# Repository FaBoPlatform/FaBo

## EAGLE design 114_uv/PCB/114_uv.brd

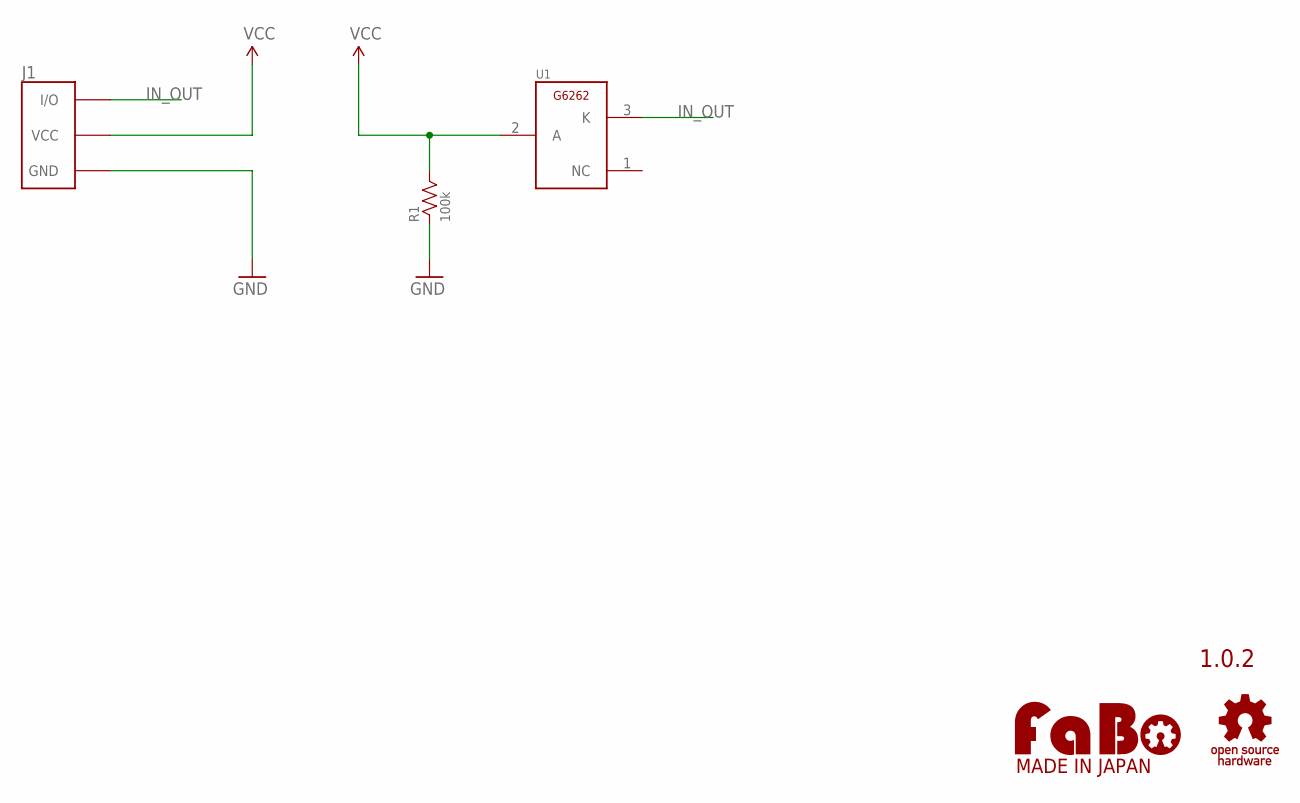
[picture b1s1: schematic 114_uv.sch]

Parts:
J1: FABO_BRICK_3PIN
R1: 100k; 0603
U1: HAMAMATSU-GAASP-G6262; GAASP-G6262
U$2: LOGO_OSHW-M_BOTTOM; LOGO_OSHW_M_BOTTOM
U$3: LOGO_FABO-M; LOGO_FABO_MS

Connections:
GND: J1.GND, R1.1
IN_OUT: J1.I/O, U1.3 (K)
VCC: J1.VCC, R1.2, U1.2 (A)

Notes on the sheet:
1.0.2

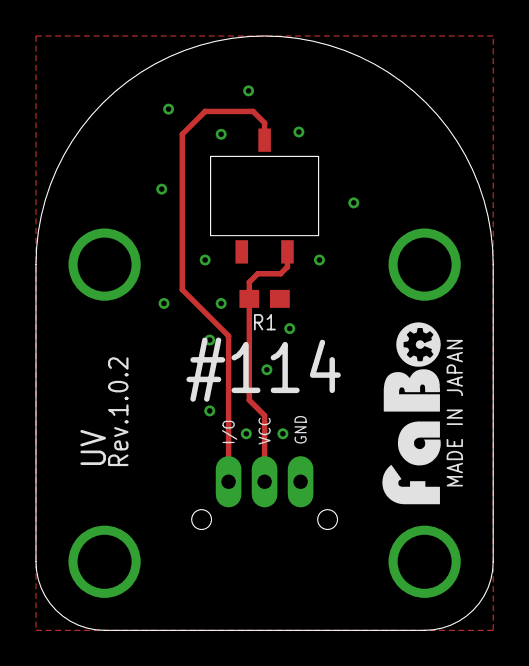
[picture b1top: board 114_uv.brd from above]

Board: 2 copper layers, 25.4 x 33.0 mm, 5 parts (0 on the bottom side), 3 nets.

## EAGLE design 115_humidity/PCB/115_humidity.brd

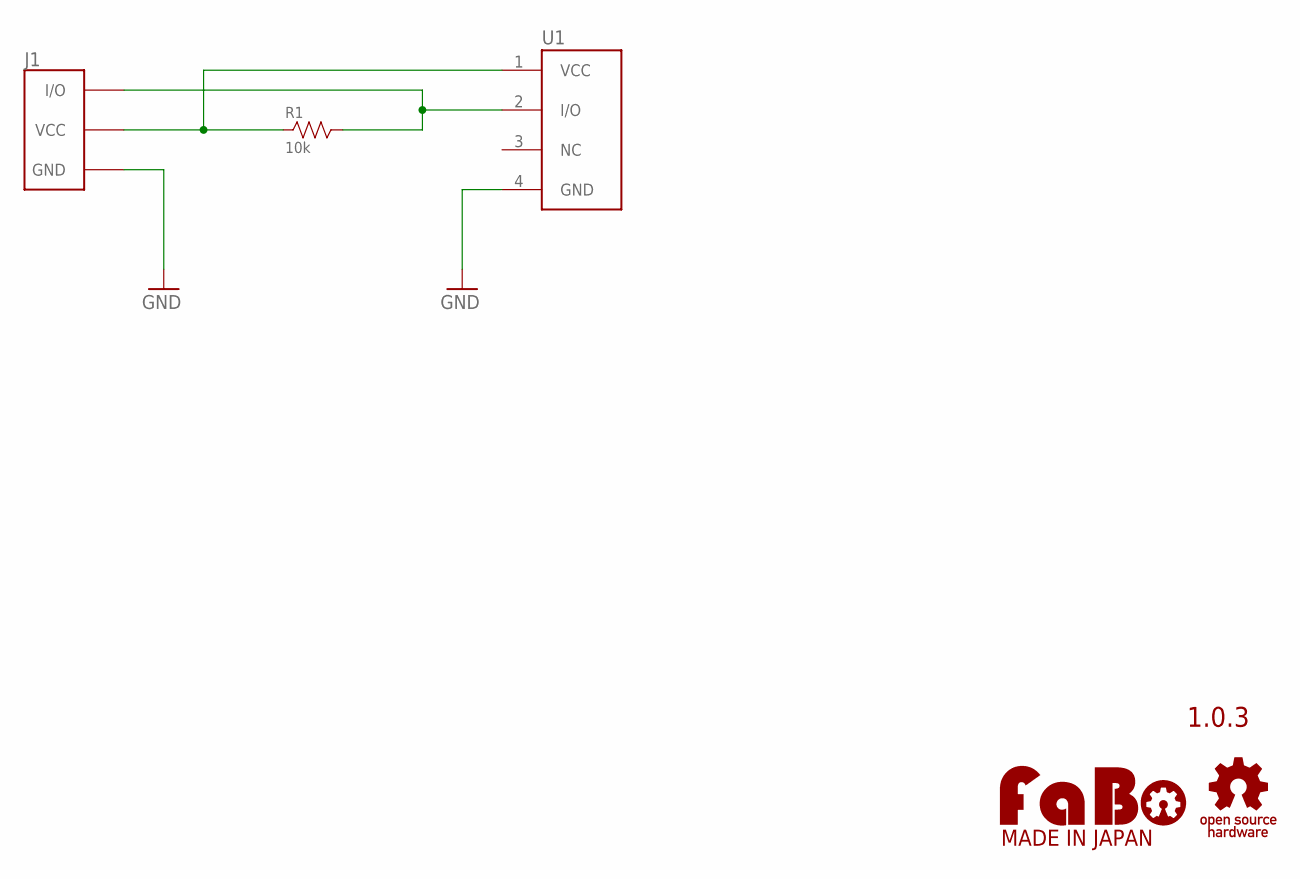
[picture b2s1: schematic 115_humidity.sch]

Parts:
J1: FABO_BRICK_3PIN
R1: 10k; AXL-REGULAR
U1: DHT11
U$2: LOGO_OSHW-M_BOTTOM; LOGO_OSHW_M_BOTTOM
U$3: LOGO_FABO-M; LOGO_FABO_MS

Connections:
GND: J1.GND, U1.4 (GND)
unnamed: J1.I/O, R1.2, U1.2 (I/O)
unnamed: J1.VCC, R1.1, U1.1 (VCC)

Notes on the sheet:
1.0.3

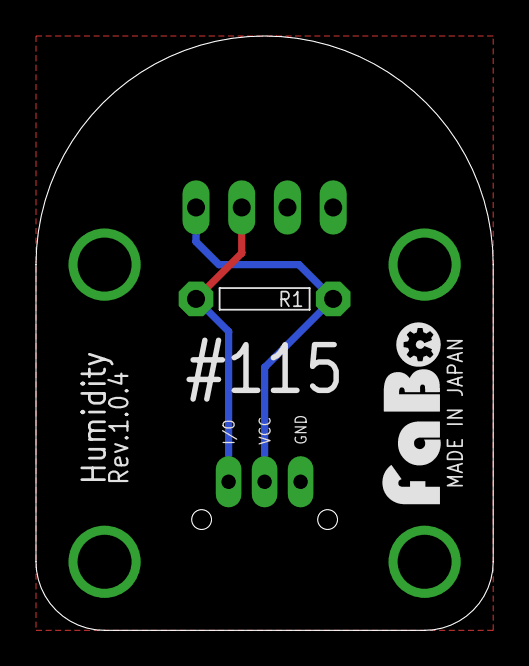
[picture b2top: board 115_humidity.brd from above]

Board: 2 copper layers, 25.4 x 33.0 mm, 5 parts (0 on the bottom side), 3 nets.

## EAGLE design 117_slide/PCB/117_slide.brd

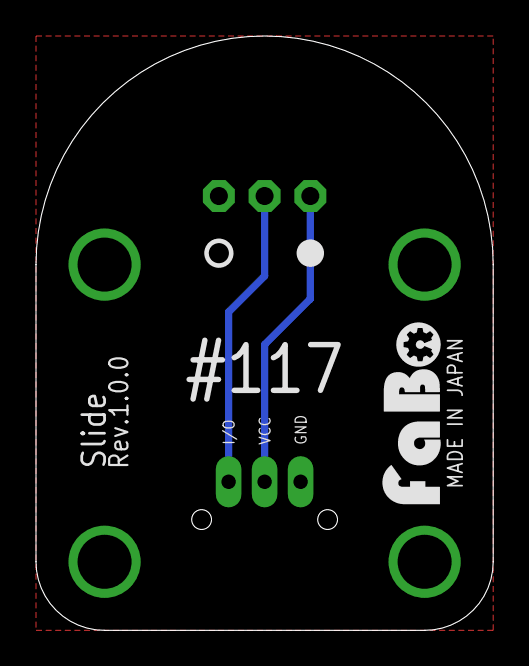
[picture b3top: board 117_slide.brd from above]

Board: 2 copper layers, 25.4 x 33.0 mm, 4 parts (0 on the bottom side), 3 nets.

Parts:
J1: FABO_BRICK_3PIN
SW1: EG1218
U$2: LOGO_OSHW_M_BOTTOM
U$4: LOGO_FABO_MS

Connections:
GND: J1.GND, SW1.1
IO: J1.I/O, SW1.2
VCC: J1.VCC, SW1.3

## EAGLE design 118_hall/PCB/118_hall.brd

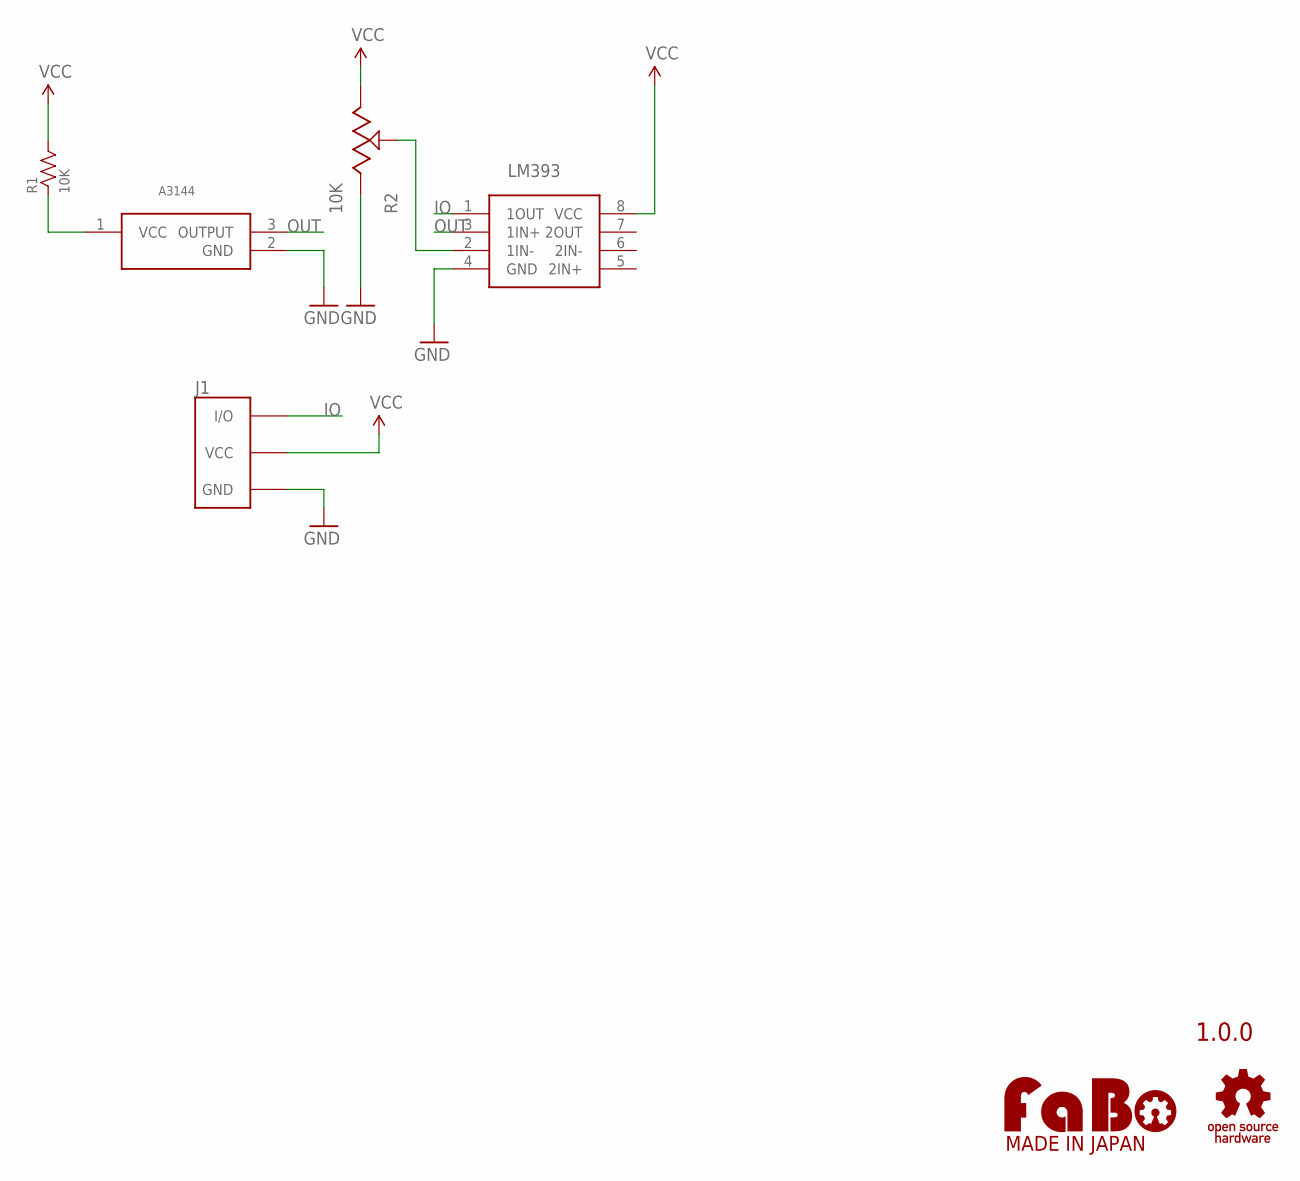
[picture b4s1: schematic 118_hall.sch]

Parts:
A3144: A3144; SOT-89
J1: FABO_BRICK_3PIN
LM393: LM393; SOIC(NARROW)-8
R1: 10K; 0603
R2: 10K; TC33X
U$2: LOGO_OSHW-M_BOTTOM; LOGO_OSHW_M_BOTTOM
U$4: LOGO_FABO-M; LOGO_FABO_MS

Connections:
GND: A3144.2 (GND), J1.GND, LM393.4 (GND), R2.3
IO: J1.I/O, LM393.1 (1OUT)
unnamed: LM393.2 (1IN-), R2.2
unnamed: A3144.1 (VCC), R1.1
OUT: A3144.3 (OUTPUT), LM393.3 (1IN+)
VCC: J1.VCC, LM393.8 (VCC), R1.2, R2.1

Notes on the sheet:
1.0.0

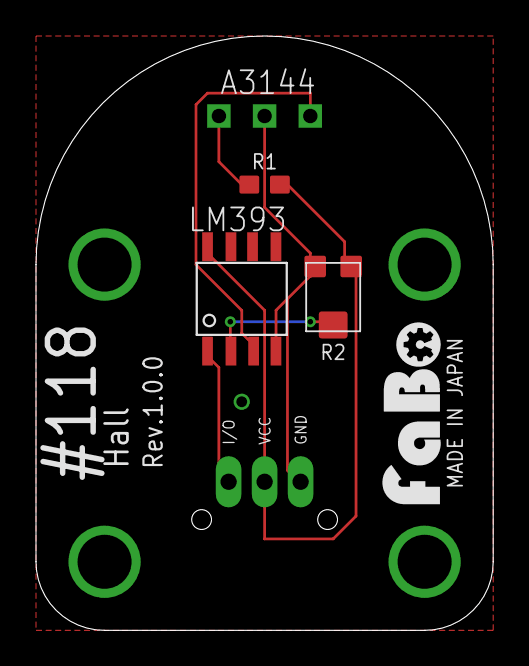
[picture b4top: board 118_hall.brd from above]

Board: 2 copper layers, 25.4 x 33.0 mm, 7 parts (0 on the bottom side), 6 nets.

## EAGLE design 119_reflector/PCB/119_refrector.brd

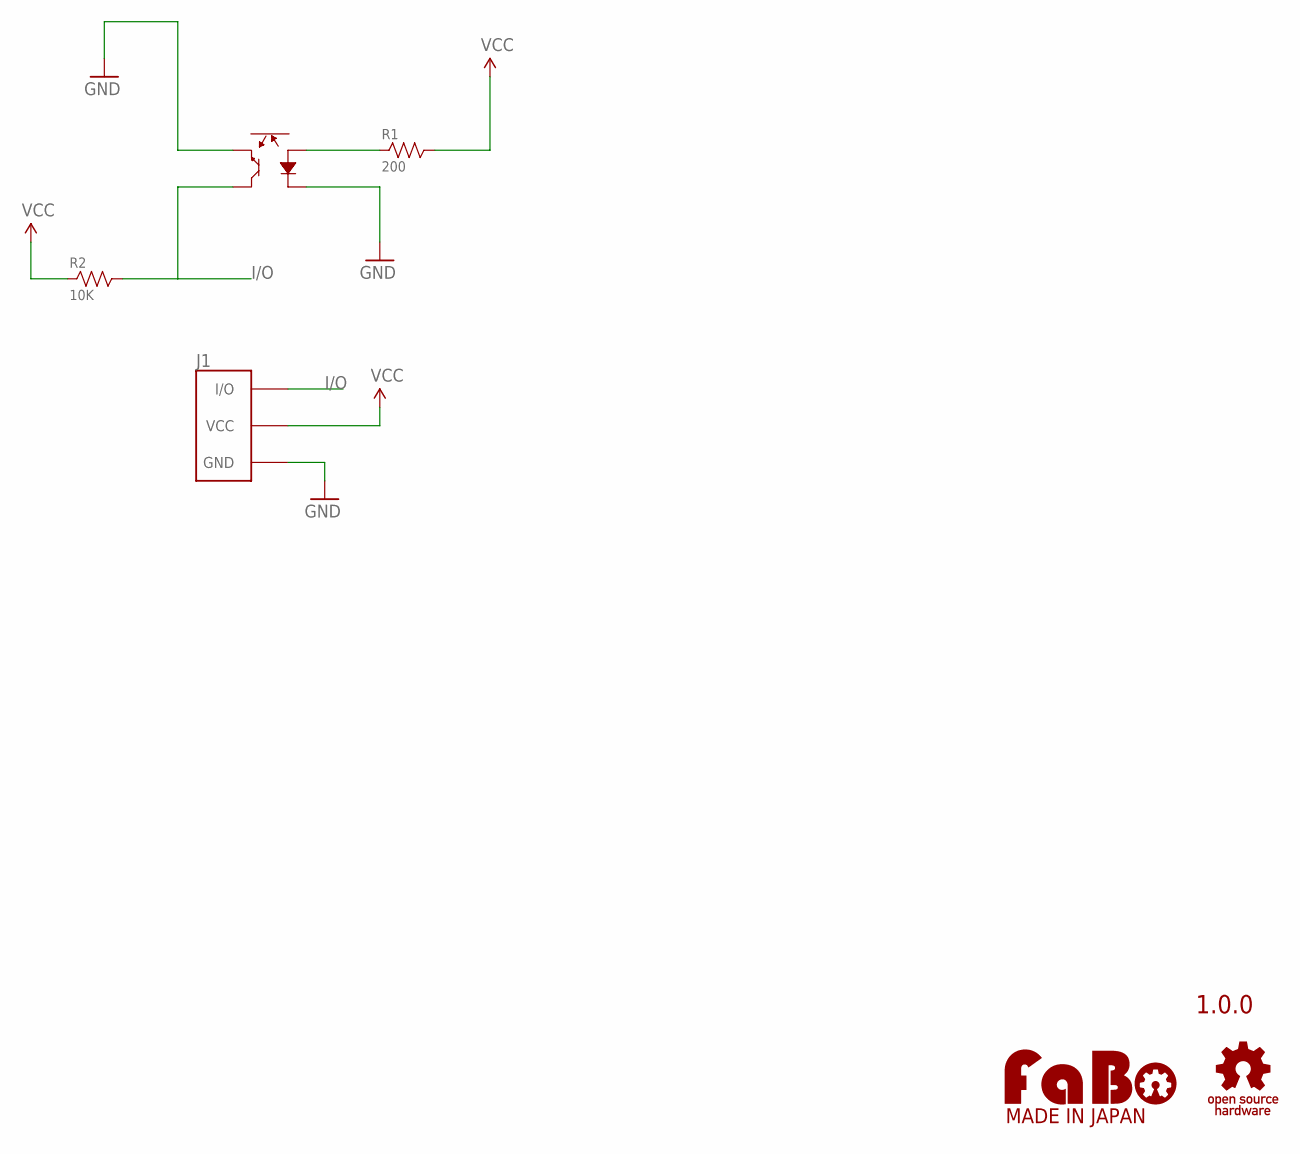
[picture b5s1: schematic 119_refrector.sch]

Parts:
J1: FABO_BRICK_3PIN
R: LBR-127HLD
R1: 200; AXL-REGULAR
R2: 10K; AXL-REGULAR
U$2: LOGO_OSHW-M_BOTTOM; LOGO_OSHW_M_BOTTOM
U$4: LOGO_FABO-M; LOGO_FABO_MS

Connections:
GND: J1.GND, R.P$2 (2), R.P$3 (3)
I/O: J1.I/O, R.P$4 (4), R2.2
unnamed: R.P$1 (1), R1.1
VCC: J1.VCC, R1.2, R2.1

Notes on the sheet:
1.0.0

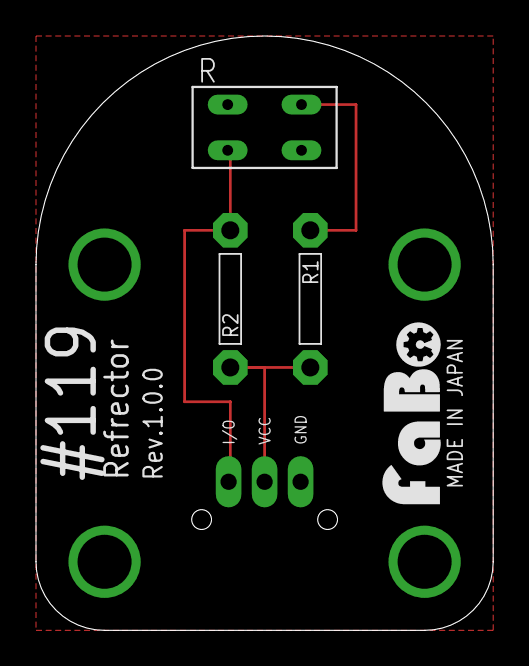
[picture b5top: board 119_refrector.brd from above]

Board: 2 copper layers, 25.4 x 33.0 mm, 6 parts (0 on the bottom side), 4 nets.

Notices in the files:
parts and their libraries:
FaBo-Template: Released under the Creative Commons Attribution-ShareAlike 4.0 License
https://creativecommons.org/licenses/by-sa/4.0
FaBo-etc: Released under the Creative Commons
